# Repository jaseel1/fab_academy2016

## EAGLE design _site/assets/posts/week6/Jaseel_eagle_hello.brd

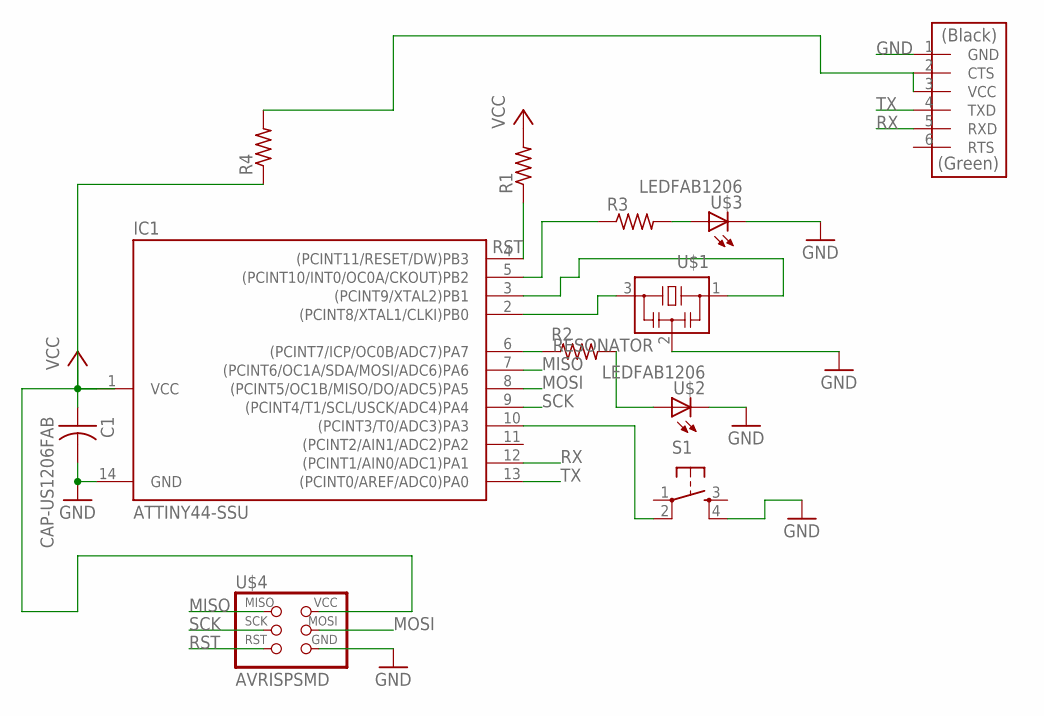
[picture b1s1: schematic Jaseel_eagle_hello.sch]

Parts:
C1: CAP-US1206FAB; C1206FAB
IC1: ATTINY44-SSU; SOIC14
R1, R2, R3, R4: RES-US1206FAB; R1206FAB
S1: 6MM_SWITCH6MM_SWITCH; 6MM_SWITCH
U$1: RESONATOR; EFOBM
U$2, U$3: LEDFAB1206; LED1206FAB
U$4: AVRISPSMD; 2X03SMD
U$5: FTDI-SMD-HEADER; 1X06SMD

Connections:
A7: IC1.6 ((PCINT7/ICP/OC0B/ADC7)PA7), R2.1
GND: C1.2, IC1.14 (GND), S1.4 (S1), U$1.2, U$2.2 (C), U$3.2 (C), U$4.6 (GND), U$5.1 (GND)
MISO: IC1.7 ((PCINT6/OC1A/SDA/MOSI/ADC6)PA6), U$4.1 (MISO)
MOSI: IC1.8 ((PCINT5/OC1B/MISO/DO/ADC5)PA5), U$4.4 (MOSI)
unnamed: IC1.2 ((PCINT8/XTAL1/CLKI)PB0), U$1.3
unnamed: IC1.3 ((PCINT9/XTAL2)PB1), U$1.1
unnamed: R2.2, U$2.1 (A)
unnamed: R3.2, U$3.1 (A)
unnamed: R4.2, U$5.3 (VCC)
unnamed: IC1.5 ((PCINT10/INT0/OC0A/CKOUT)PB2), R3.1
unnamed: IC1.10 ((PCINT3/T0/ADC3)PA3), S1.2 (P1)
RST: IC1.4 ((PCINT11/RESET/DW)PB3), R1.1, U$4.5 (RST)
RX: IC1.12 ((PCINT1/AIN0/ADC1)PA1), U$5.5 (RXD)
SCK: IC1.9 ((PCINT4/T1/SCL/USCK/ADC4)PA4), U$4.3 (SCK)
TX: IC1.13 ((PCINT0/AREF/ADC0)PA0), U$5.4 (TXD)
VCC: C1.1, IC1.1 (VCC), R1.2, R4.1

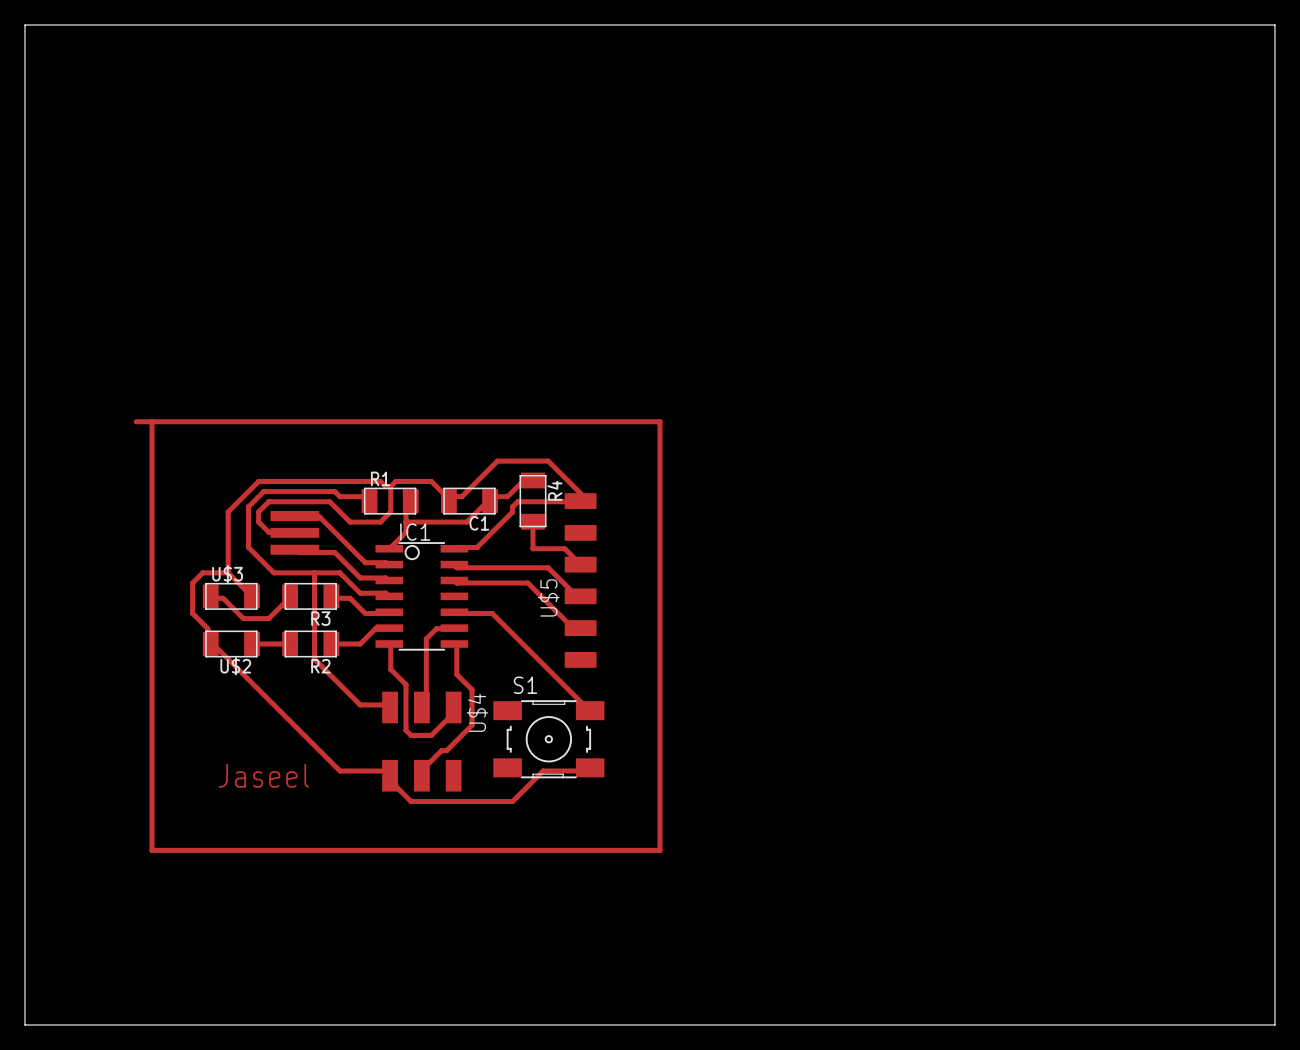
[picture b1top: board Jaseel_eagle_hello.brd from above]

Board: 2 copper layers, 100.0 x 80.0 mm, 12 parts (0 on the bottom side), 16 nets.

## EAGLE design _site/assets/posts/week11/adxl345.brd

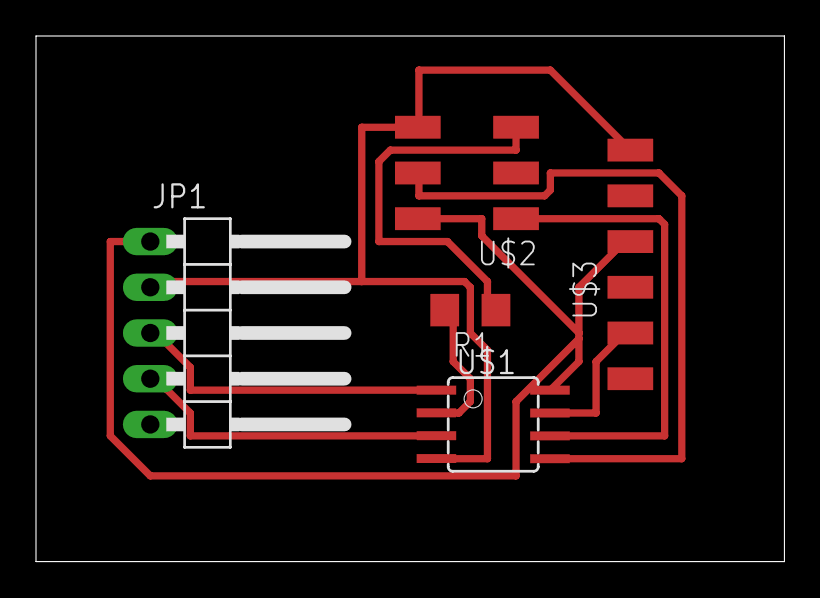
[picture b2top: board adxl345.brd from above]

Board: 2 copper layers, 41.6 x 29.2 mm, 5 parts (0 on the bottom side), 9 nets.

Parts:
JP1: 1X05/90
R1: R1206
U$1: ATTINY45SI; SOIC8
U$2: AVRISPSMD; 2X03SMD
U$3: FTDI-SMD-HEADER; 1X06SMD

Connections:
GND: JP1.2, U$1.4, U$2.6, U$3.1
MISO: U$1.6, U$2.1
MOSI: U$1.5, U$2.4
unnamed: R1.2, U$1.2
RST: R1.1, U$2.5
RX: U$1.7, U$3.5
SCL: JP1.3, U$1.1
SDA: JP1.4, U$1.3
VCC: JP1.1, U$1.8, U$2.2, U$3.3

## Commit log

2016-05-19 hello
